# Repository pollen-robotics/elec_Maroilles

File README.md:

# "Maroilles" Electronic Board

"elec_maroilles" is USB 2.0 hub built with lockable USB connectors. It provides also Dynamixel TTL and Dynamixel RS485 converters and the associated connectors for Reachy 2's grippers and antennas.

## Basically
 - Designed with KiCAD 9.

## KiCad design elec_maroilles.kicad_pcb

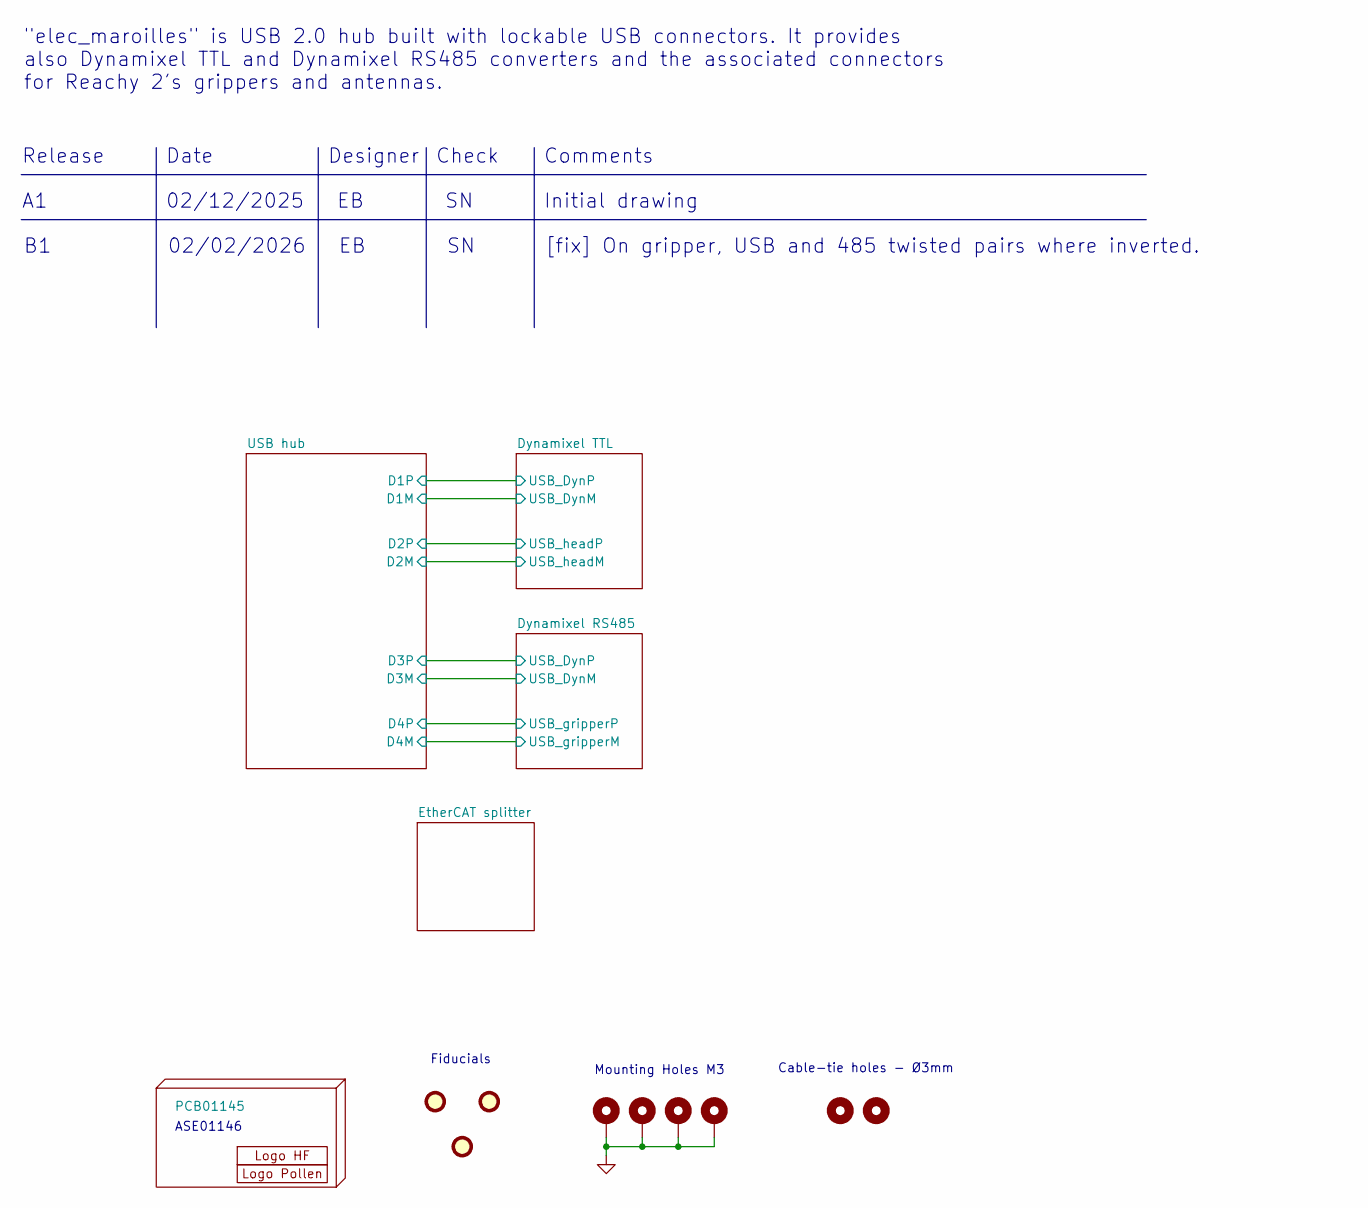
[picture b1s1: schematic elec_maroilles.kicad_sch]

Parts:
FID1, FID2, FID3: DNP Fiducial; Fiducial_1mm_Mask2mm
H1: PCB01145
H2: Logo HF 2025; Logo_HF_2025
H3: DNP Logo Pollen 2021; Logo_Pollen_2021_sq
H4, H5, H6, H7: MountingHole_Pad; MountingHole_3.2mm_M3_ISO7380_Pad_TopBottom
H10, H11: MountingHole_Pad; MountingHole_3.2mm_M3

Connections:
GND: H4.1, H5.1, H6.1, H7.1; also elsewhere on the board

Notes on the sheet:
Mounting Holes M3
Date
Check
Release
Fiducials
ASE01146
Cable-tie holes - Ø3mm
Initial drawing
[fix] On gripper, USB and 485 twisted pairs where inverted.
"elec_maroilles" is USB 2.0 hub built with lockable USB connectors. It provides also Dynamixel TTL and Dynamixel RS485 converters and the associated connectors for Reachy 2's grippers and antennas.
02/02/2026
Designer
Comments
02/12/2025

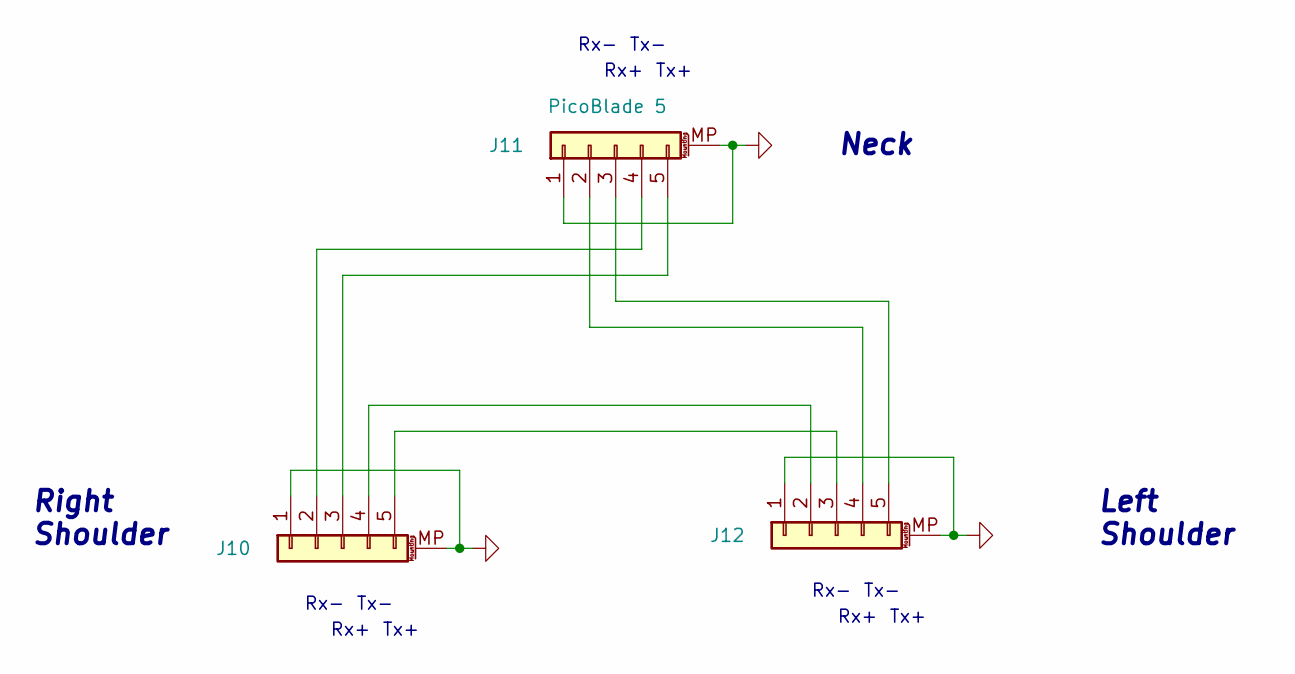
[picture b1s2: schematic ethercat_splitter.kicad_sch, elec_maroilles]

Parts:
J10, J11, J12: PicoBlade 5; Molex_PicoBlade_53398-0571_1x05-1MP_P1.25mm_Vertical; LCSC Part C504986

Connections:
GND: J10.1, J10.MP (MountPin), J11.1, J11.MP (MountPin), J12.1, J12.MP (MountPin); also elsewhere on the board
unnamed: J10.2, J11.4
unnamed: J10.3, J11.5
unnamed: J10.4, J12.2
unnamed: J10.5, J12.3
unnamed: J11.2, J12.4
unnamed: J11.3, J12.5

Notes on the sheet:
Rx-
Tx-
Right Shoulder
Rx+
Left Shoulder
Neck
Tx+

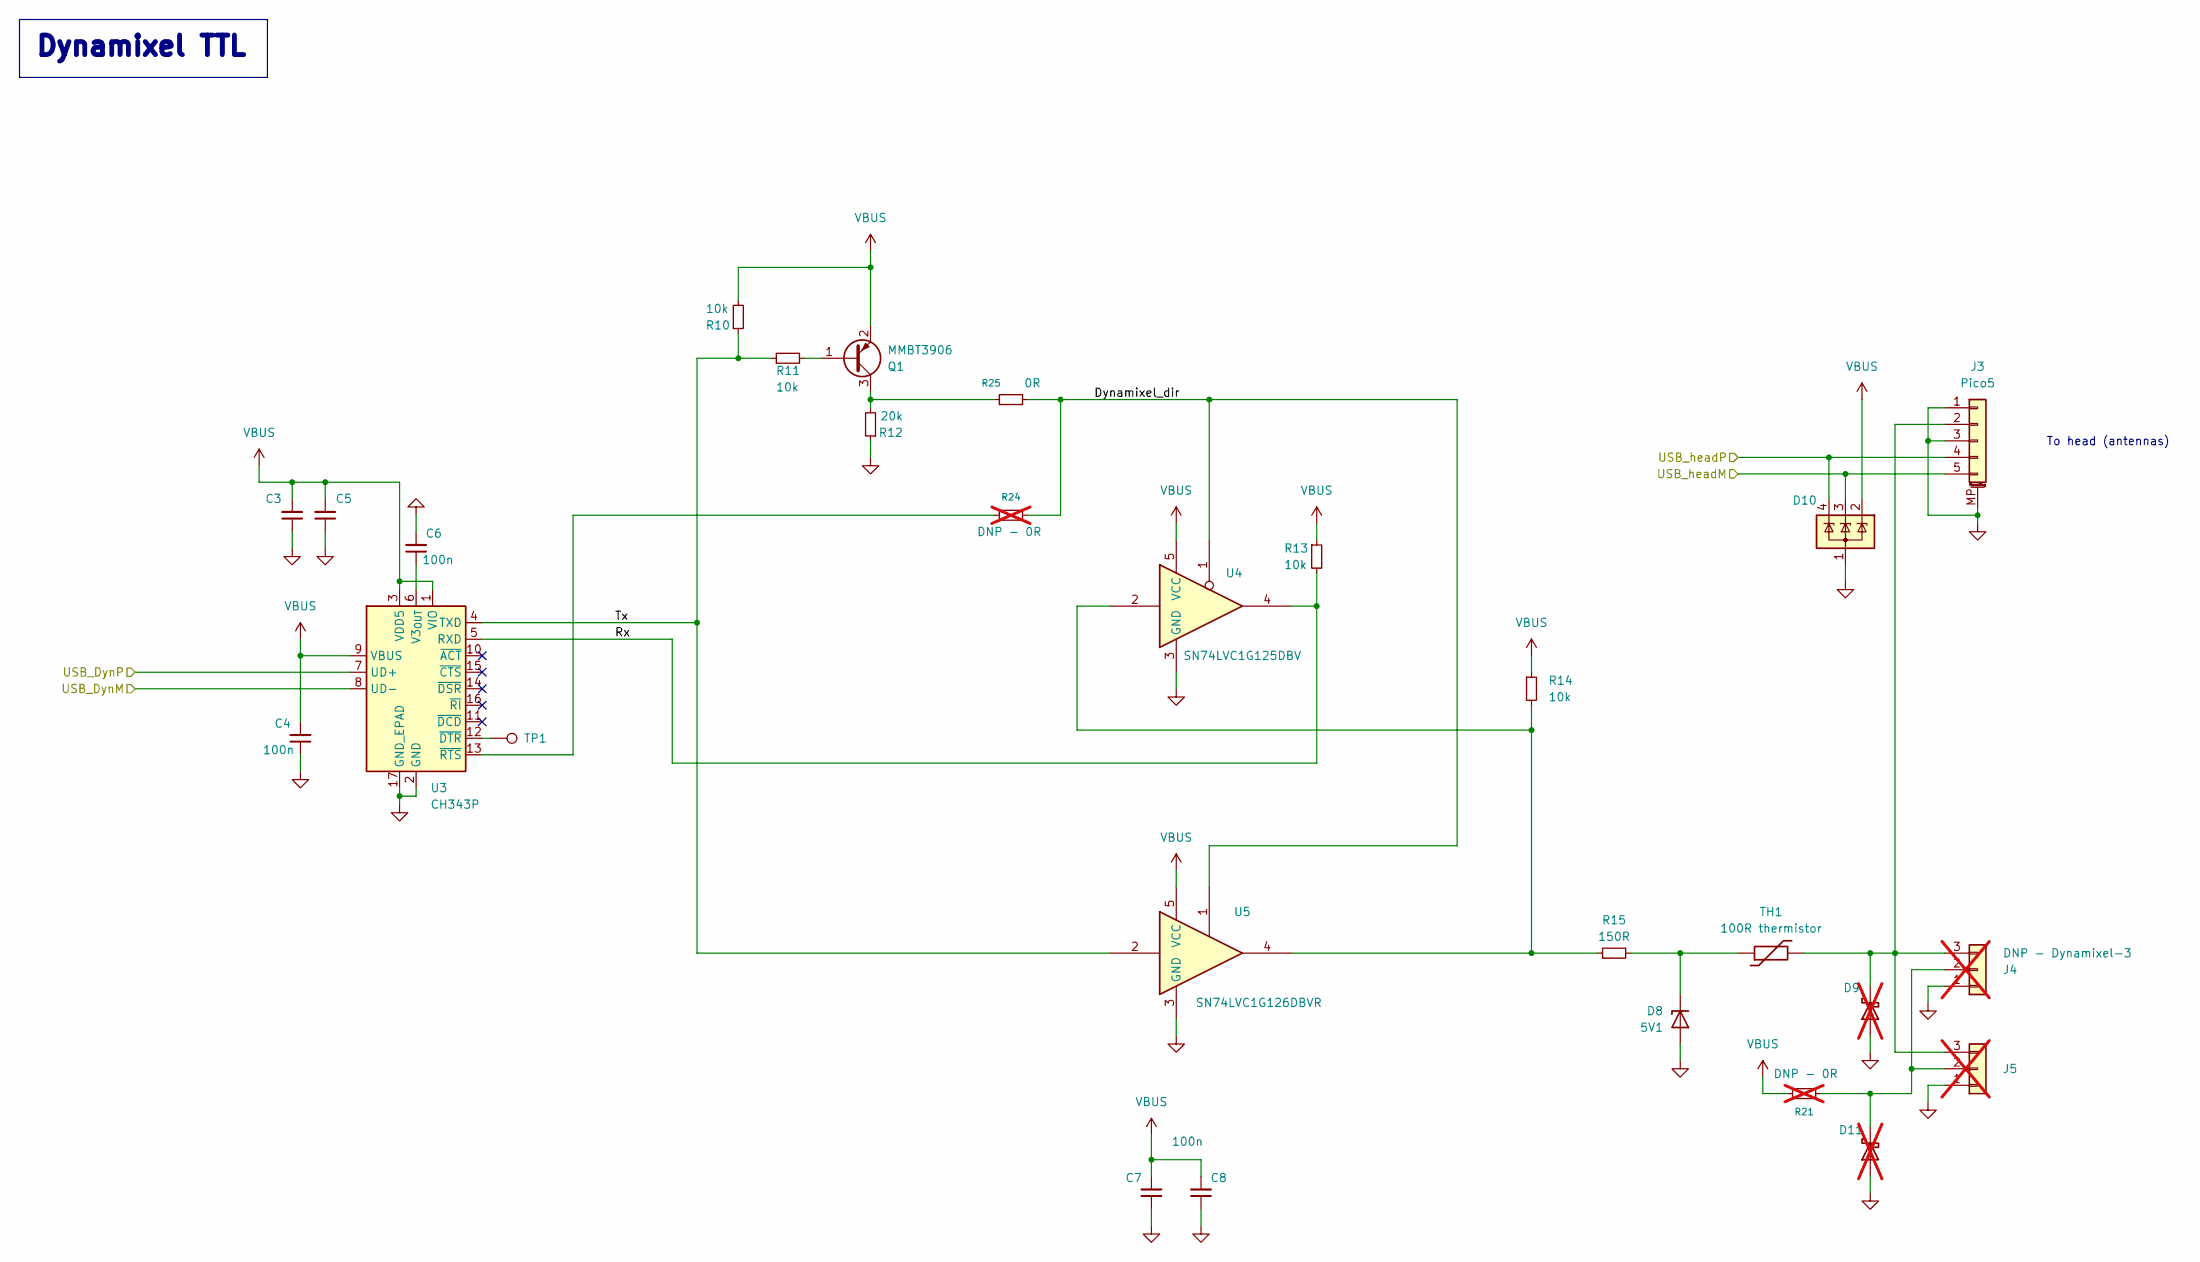
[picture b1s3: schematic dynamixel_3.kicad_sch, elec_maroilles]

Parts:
C3, C5: 1uF-6V3; C_0603_1608Metric; LCSC Part C1592
C4, C6, C7, C8: 100n; C_0603_1608Metric; LCSC Part C85864
D8: 5V1; D_SOD-323; LCSC Part C151348
D9, D11: DNP - B5819WS; D_SOD-323; LCSC Part C78734; not fitted
D10: SP0503BAHT; SOT-143; LCSC Part C41364459
J3: Pico5; Molex_PicoBlade_53398-0571_1x05-1MP_P1.25mm_Vertical; LCSC Part C504986
J4, J5: DNP - Dynamixel-3; JST_EH_B3B-EH-A_1x03_P2.50mm_Vertical; LCSC Part C160259; not fitted
Q1: MMBT3906; SOT-23; LCSC Part C727128
R10, R11, R13, R14: 10k; R_0402_1005Metric; LCSC Part C25744
R12: 20k; R_0402_1005Metric; LCSC Part C2906867
R15: 150R; R_0402_1005Metric; LCSC Part C138054
R21: DNP - 0R; R_0402_1005Metric; not fitted
R24: DNP - 0R; R_0402_1005Metric; LCSC Part C17168; not fitted
R25: 0R; R_0402_1005Metric; LCSC Part C17168
TH1: 100R thermistor; R_0603_1608Metric; LCSC Part C913703
TP1: TestPoint; TestPoint_Pad_D1.0mm
U3: CH343P; WCH_QFN-16-1EP_3x3mm_P0.5mm_EP1.8x1.8mm; LCSC Part C2846043
U4: SN74LVC1G125DBV; SOT-23-5; LCSC Part C23654
U5: SN74LVC1G126DBVR; SOT-23-5; LCSC Part C7834

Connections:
/Dynamixel TTL/Dynamixel_dir: R24.2, R25.2, U4.1, U5.1
/Dynamixel TTL/Rx: R13.2, U3.5 (RXD), U4.4
/Dynamixel TTL/Tx: R10.1, R11.1, U3.4 (TXD), U5.2
/Dynamixel TTL/USB_DynM: U3.8 (UD-); also elsewhere on the board
/Dynamixel TTL/USB_DynP: U3.7 (UD+); also elsewhere on the board
/Dynamixel TTL/USB_headM: D10.3 (K), J3.5; also elsewhere on the board
/Dynamixel TTL/USB_headP: D10.4 (K), J3.4; also elsewhere on the board
GND: C3.1, C4.1, C5.1, C6.2, C7.1, C8.1, D8.2 (A), D9.2 (A), D10.1 (A), D11.2 (A), J3.1, J3.3, J3.MP (MountPin), J4.1, J5.1, R12.1, U3.2 (GND), U3.17 (GND_EPAD), U4.3 (GND), U5.3 (GND); also elsewhere on the board
unnamed: D8.1 (K), R15.2, TH1.1
unnamed: D9.1 (K), J3.2, J4.3, J5.3, TH1.2
unnamed: D11.1 (K), J4.2, J5.2, R21.2
unnamed: Q1.1 (B), R11.2
unnamed: Q1.3 (C), R12.2, R25.1
unnamed: R14.2, R15.1, U4.2, U5.4
unnamed: C6.1, U3.6 (V3_{OUT})
unnamed: TP1.1, U3.12 (~DTR)
unnamed: R24.1, U3.13 (~RTS)
VBUS: C3.2, C4.2, C5.2, C7.2, C8.2, D10.2 (K), Q1.2 (E), R10.2, R13.1, R14.1, R21.1, U3.1 (VIO), U3.3 (VDD5), U3.9 (VBUS), U4.5 (VCC), U5.5 (VCC); also elsewhere on the board

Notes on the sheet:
To head (antennas)
Dynamixel TTL

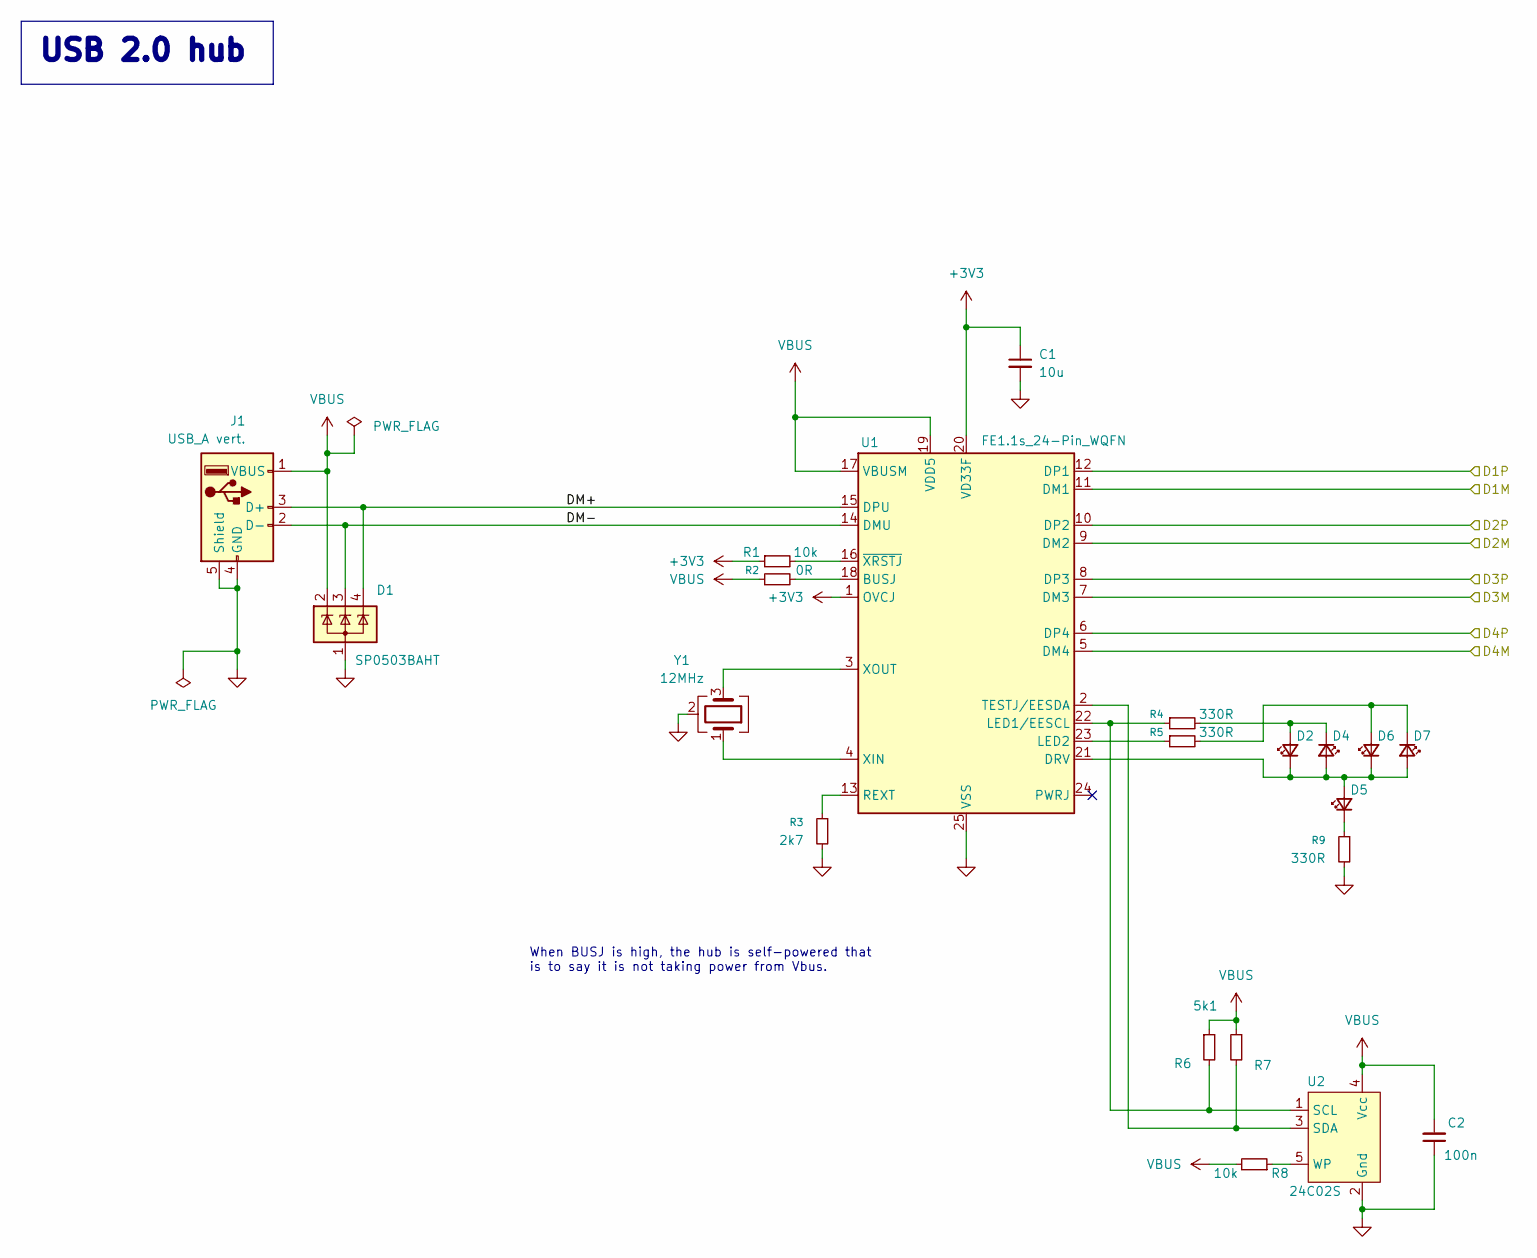
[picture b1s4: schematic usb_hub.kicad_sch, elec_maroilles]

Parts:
C1: 10u; C_0603_1608Metric; LCSC Part C1691
C2: 100n; C_0603_1608Metric; LCSC Part C85864
D1: SP0503BAHT; SOT-143; LCSC Part C41364459
D2, D6: LED_Small; LED_0603_1608Metric; LCSC Part C19171301
D4, D7: LED_Small; LED_0603_1608Metric; LCSC Part C84263
D5: LED_Small; LED_0603_1608Metric; LCSC Part C7429915
J1: USB_A vert.; Amphenol_LUSBA11100; LCSC Part C3197751
R1, R8: 10k; R_0402_1005Metric; LCSC Part C25744
R2: 0R; R_0402_1005Metric; LCSC Part C17168
R3: 2k7; R_0402_1005Metric; LCSC Part C138017
R4, R5, R9: 330R; R_0402_1005Metric; LCSC Part C105875
R6, R7: 5k1; R_0402_1005Metric; LCSC Part C25905
U1: FE1.1s_24-Pin_WQFN; WQFN-24-1EP_4x4mm_P0.5mm_EP2.6x2.6mm; LCSC Part C6776948
U2: 24C02S; SOT-23-5; LCSC Part C18723540
Y1: 12MHz; Crystal_SMD_3225-4Pin_3.2x2.5mm; LCSC Part C133334

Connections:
+3V3: C1.1, R1.1, U1.1 (OVCJ), U1.20 (VD33F)
/Dynamixel RS485/USB_DynM: U1.7 (DM3); also elsewhere on the board
/Dynamixel RS485/USB_DynP: U1.8 (DP3); also elsewhere on the board
/Dynamixel RS485/USB_gripperM: U1.5 (DM4); also elsewhere on the board
/Dynamixel RS485/USB_gripperP: U1.6 (DP4); also elsewhere on the board
/Dynamixel TTL/USB_DynM: U1.11 (DM1); also elsewhere on the board
/Dynamixel TTL/USB_DynP: U1.12 (DP1); also elsewhere on the board
/Dynamixel TTL/USB_headM: U1.9 (DM2); also elsewhere on the board
/Dynamixel TTL/USB_headP: U1.10 (DP2); also elsewhere on the board
/USB hub/DM+: D1.4 (K), J1.3 (D+), U1.15 (DPU)
/USB hub/DM-: D1.3 (K), J1.2 (D-), U1.14 (DMU)
GND: C1.2, C2.1, D1.1 (A), J1.4 (GND), J1.5 (Shield), R3.2, R9.2, U1.25 (VSS), U2.2 (Gnd), Y1.2 (G), Y1.4 (G); also elsewhere on the board
unnamed: D2.2 (A), D4.1 (K), R4.2
unnamed: D2.1 (K), D4.2 (A), D5.2 (A), D6.1 (K), D7.2 (A), U1.21 (DRV)
unnamed: D5.1 (K), R9.1
unnamed: D6.2 (A), D7.1 (K), R5.2
unnamed: R2.2, U1.18 (BUSJ)
unnamed: R4.1, R6.2, U1.22 (LED1/EESCL), U2.1 (SCL)
unnamed: R5.1, U1.23 (LED2)
unnamed: R3.1, U1.13 (REXT)
unnamed: R7.2, U1.2 (TESTJ/EESDA), U2.3 (SDA)
unnamed: U1.4 (XIN), Y1.1
unnamed: U1.3 (XOUT), Y1.3
unnamed: R1.2, U1.16 (~XRSTJ)
unnamed: R8.1, U2.5 (WP)
VBUS: C2.2, D1.2 (K), J1.1 (VBUS), R2.1, R6.1, R7.1, R8.2, U1.17 (VBUSM), U1.19 (VDD5), U2.4 (Vcc); also elsewhere on the board

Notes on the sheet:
When BUSJ is high, the hub is self-powered that is to say it is not taking power from Vbus.
USB 2.0 hub

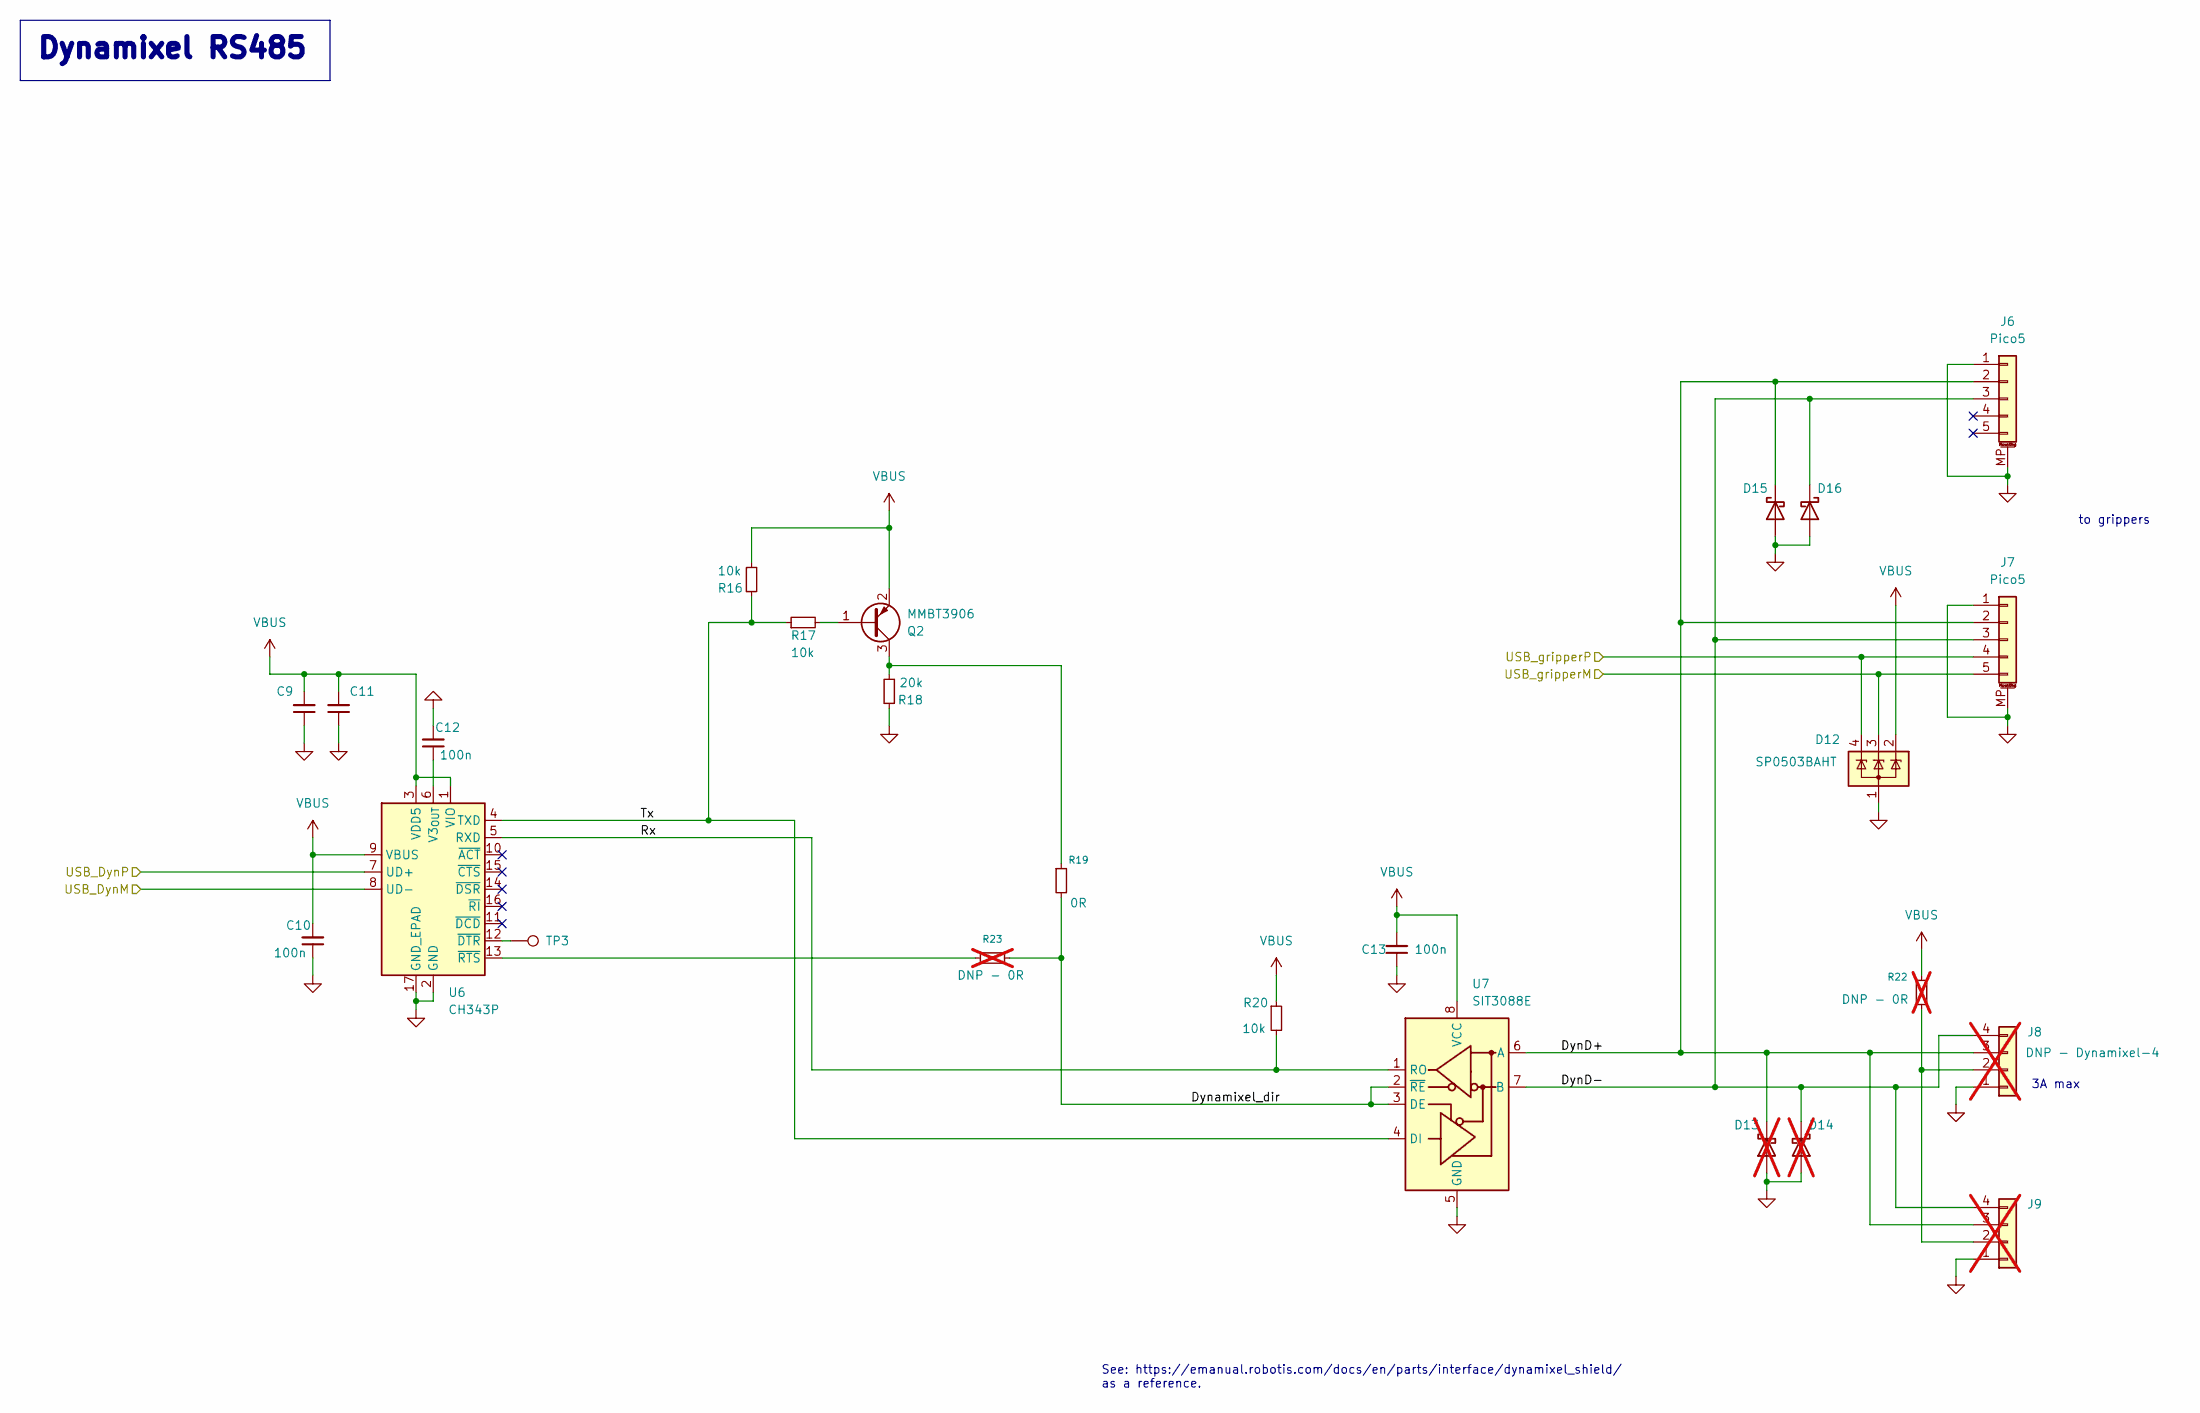
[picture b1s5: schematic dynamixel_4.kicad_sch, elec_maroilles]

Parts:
C9, C11: 1uF-6V3; C_0603_1608Metric; LCSC Part C1592
C10, C12, C13: 100n; C_0603_1608Metric; LCSC Part C85864
D12: SP0503BAHT; SOT-143; LCSC Part C41364459
D13, D14: DNP - B5819WS; D_SOD-323; LCSC Part C78734; not fitted
D15, D16: B5819WS; D_SOD-323; LCSC Part C78734
J6, J7: Pico5; Molex_PicoBlade_53398-0571_1x05-1MP_P1.25mm_Vertical; LCSC Part C504986
J8, J9: DNP - Dynamixel-4; JST_EH_B4B-EH-A_1x04_P2.50mm_Vertical; LCSC Part C160258; not fitted
Q2: MMBT3906; SOT-23; LCSC Part C727128
R16, R17, R20: 10k; R_0402_1005Metric; LCSC Part C25744
R18: 20k; R_0402_1005Metric; LCSC Part C2906867
R19: 0R; R_0402_1005Metric; LCSC Part C17168
R22: DNP - 0R; R_0402_1005Metric; not fitted
R23: DNP - 0R; R_0402_1005Metric; LCSC Part C17168; not fitted
TP3: TestPoint; TestPoint_Pad_D1.0mm
U6: CH343P; WCH_QFN-16-1EP_3x3mm_P0.5mm_EP1.8x1.8mm; LCSC Part C2846043
U7: SIT3088E; DFN-8-1EP_3x3mm_P0.65mm_EP1.5x2.25mm; LCSC Part C601076

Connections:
/Dynamixel RS485/DynD+: D13.1 (K), D15.1 (K), J6.2, J7.2, J8.3, J9.3, U7.6 (A)
/Dynamixel RS485/DynD-: D14.1 (K), D16.1 (K), J6.3, J7.3, J8.4, J9.4, U7.7 (B)
/Dynamixel RS485/Dynamixel_dir: R19.2, R23.2, U7.2 (~RE), U7.3 (DE)
/Dynamixel RS485/Rx: R20.2, U6.5 (RXD), U7.1 (RO)
/Dynamixel RS485/Tx: R16.1, R17.1, U6.4 (TXD), U7.4 (DI)
/Dynamixel RS485/USB_DynM: U6.8 (UD-); also elsewhere on the board
/Dynamixel RS485/USB_DynP: U6.7 (UD+); also elsewhere on the board
/Dynamixel RS485/USB_gripperM: D12.3 (K), J7.5; also elsewhere on the board
/Dynamixel RS485/USB_gripperP: D12.4 (K), J7.4; also elsewhere on the board
GND: C9.1, C10.1, C11.1, C12.2, C13.1, D12.1 (A), D13.2 (A), D14.2 (A), D15.2 (A), D16.2 (A), J6.1, J6.MP (MountPin), J7.1, J7.MP (MountPin), J8.1, J9.1, R18.1, U6.2 (GND), U6.17 (GND_EPAD), U7.5 (GND); also elsewhere on the board
unnamed: J8.2, J9.2, R22.2
unnamed: Q2.1 (B), R17.2
unnamed: Q2.3 (C), R18.2, R19.1
unnamed: C12.1, U6.6 (V3_{OUT})
unnamed: TP3.1, U6.12 (~DTR)
unnamed: R23.1, U6.13 (~RTS)
VBUS: C9.2, C10.2, C11.2, C13.2, D12.2 (K), Q2.2 (E), R16.2, R20.1, R22.1, U6.1 (VIO), U6.3 (VDD5), U6.9 (VBUS), U7.8 (VCC); also elsewhere on the board

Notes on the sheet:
See: https://emanual.robotis.com/docs/en/parts/interface/dynamixel_shield/ as a reference.
3A max
to grippers
Dynamixel RS485

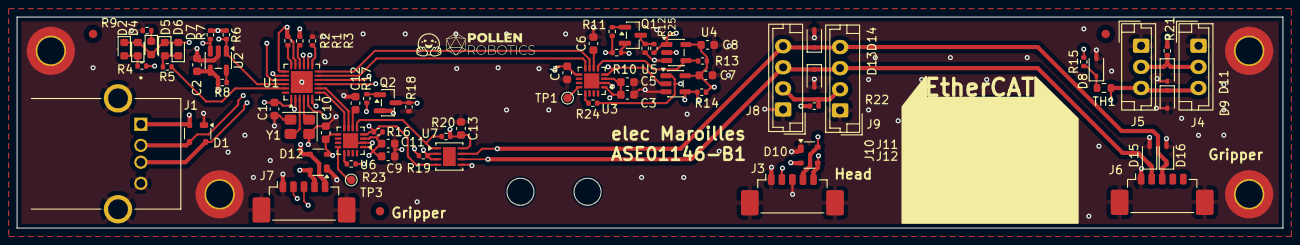
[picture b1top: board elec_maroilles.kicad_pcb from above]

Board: 4 copper layers, 150.0 x 25.0 mm, 88 parts (0 on the bottom side), 55 nets.

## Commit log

2025-11-27 [init] Initial commit, schematic is not too bad.
2025-11-28 [update] Positionning v1
2025-12-02 [update] Better positionning.
2025-12-02 [update] Release A1 -> in production at JLCPCB qtty 5
2025-12-30 [error] To be fixed: inverted diff pairs on grippers pico5.
2026-02-02 [update] Release B1!
